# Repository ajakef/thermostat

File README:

The thermostat pcb is a bit more general than the name suggests: basically, it's a shield for turning any device on and off depending on the reading of one or two sensors, according to rules programmed in Arduino code.

It requires 120/240 V AC power and a load current of less than 10 A. The max load current can be increased to 15 A by swapping in a slightly more expensive relay. A built-in AC-DC converter (again, 120/240 V) powers the Arduino and shield with up to 1 W (more than enough for most Arduino applications).

The user is responsible for cutting a power cord and connecting it to the correct screw terminals; color-coding and text labels make this safe and straightforward.

The shield is intended to work with thermistors connected to screw terminals. However, any passive analog sensor compatible with the Arduino's ADC can also be connected to the screw terminal, and a powered analog sensor can also be used by soldering the 5V lead to the board.

Schematic symbols are all stored in thermostat.lib. Component footprints are all stored in thermostat.pretty/. There should be no library issues.

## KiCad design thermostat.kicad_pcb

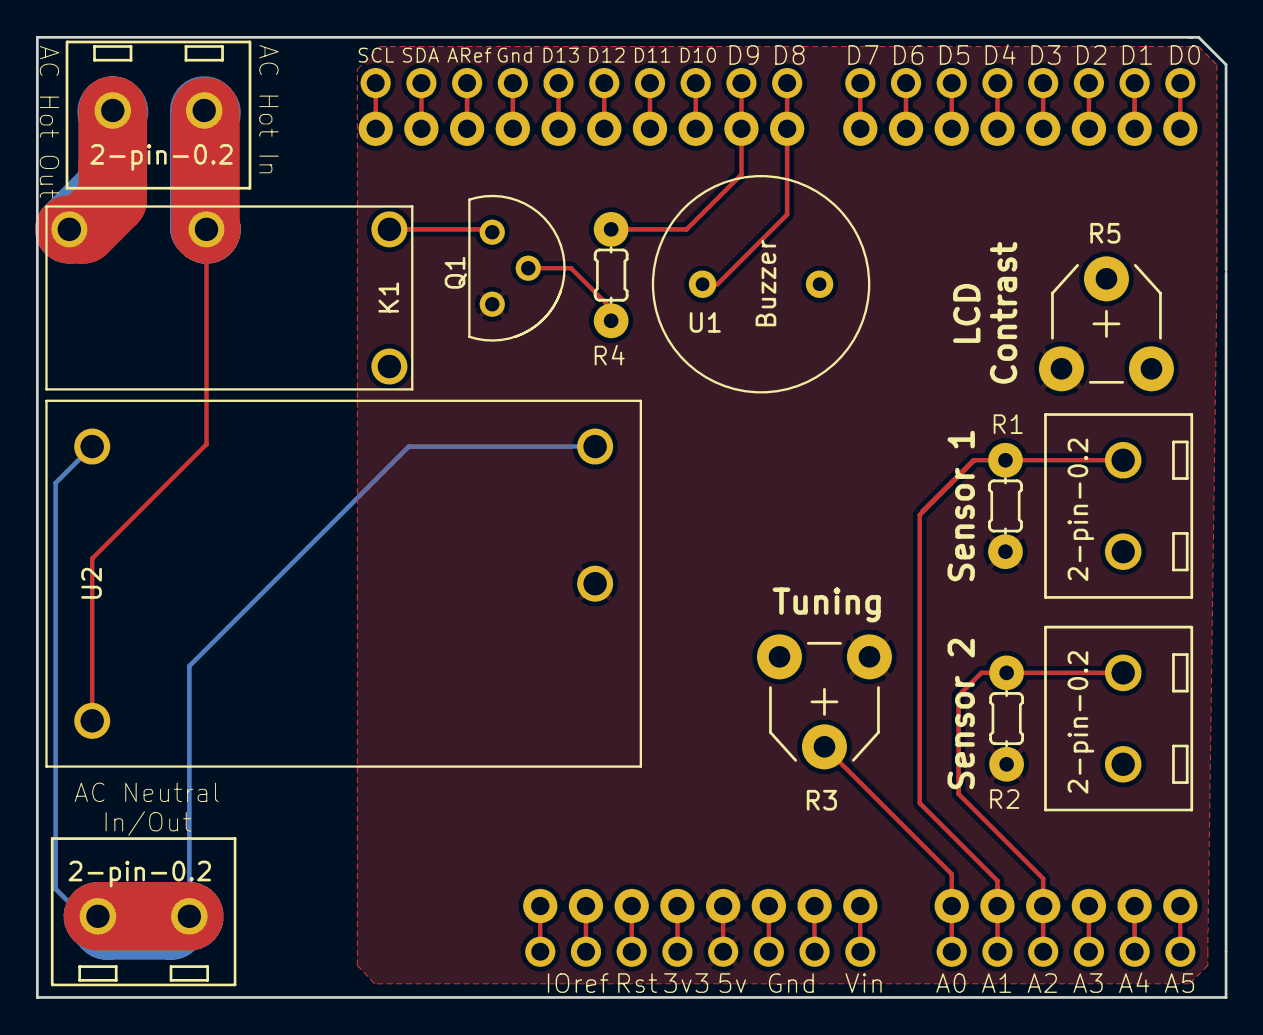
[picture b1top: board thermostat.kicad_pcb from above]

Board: 2 copper layers, 66.0 x 53.3 mm, 46 parts (0 on the bottom side), 34 nets.

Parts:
K1: RELAY_SPST; Relay-SPST-0.3-0.4
M1: ARDUINOUNOR3-JFA; ARDUINOR3-JFA
PAD1, PAD2, PAD3, PAD4, PAD5, PAD6, PAD7, PAD8, PAD9, PAD10, PAD11, PAD12, PAD13, PAD14, PAD15, PAD16, PAD17, PAD18, PAD19, PAD20, PAD21, PAD22, PAD23, PAD24, PAD25, PAD26, PAD27, PAD28, PAD29, PAD30, PAD31, PAD32: WIREPAD2_15_1_0; 2_15_1_0
Q1: PN2222A; transistor
R1, R2: 100k; R_0.2
R3, R5: POT; Potentiometer_VishaySpectrol-Econtrim-Type36T
R4: 1k; R_0.2
U1: Buzzer; Buzzer-6.5mm
U2: AC-DC-Converter; AC-DC-RAC01-GA
U3, U4, U5, U6: 2-pin-0.2

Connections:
120VAC: K1.2, U2.1, U5.1
+5V: M1.5V, PAD15.1, Q1.3, R1.2, R2.1, R3.1, R5.1, U2.4
Earth: K1.5, M1.GND, M1.GND1, M1.GND2, PAD4.1, PAD16.1, PAD18.1, R3.3, R5.3, U1.2, U2.2, U2.3, U3.1, U4.1, U6.1, U6.2
unnamed: K1.1, Q1.1
unnamed: K1.3, U5.2
unnamed: M1.3V, PAD13.1
unnamed: M1.A0, PAD23.1, R3.2
unnamed: M1.A1, PAD25.1, R1.1, U3.2
unnamed: M1.A2, PAD27.1, R2.2, U4.2
unnamed: M1.A3, PAD29.1
unnamed: M1.A4, PAD31.1
unnamed: M1.A5, PAD32.1
unnamed: M1.AREF, PAD3.1
unnamed: M1.D0, PAD30.1
unnamed: M1.D1, PAD28.1
unnamed: M1.D2, PAD26.1
unnamed: M1.D3, PAD24.1
unnamed: M1.D4, PAD22.1
unnamed: M1.D5, PAD21.1
unnamed: M1.D6, PAD19.1
unnamed: M1.D7, PAD17.1
unnamed: M1.D8, PAD14.1, U1.1
unnamed: M1.D9, PAD12.1, R4.2
unnamed: M1.D10, PAD10.1
unnamed: M1.D11, PAD8.1
unnamed: M1.D12, PAD6.1
unnamed: M1.D13, PAD5.1
unnamed: M1.IORE, PAD9.1
unnamed: M1.NC, PAD7.1
unnamed: M1.RESE, PAD11.1
unnamed: M1.SCL, PAD1.1
unnamed: M1.SDA, PAD2.1
unnamed: M1.VIN, PAD20.1
unnamed: Q1.2, R4.1

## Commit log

2018-04-24 add BOM
